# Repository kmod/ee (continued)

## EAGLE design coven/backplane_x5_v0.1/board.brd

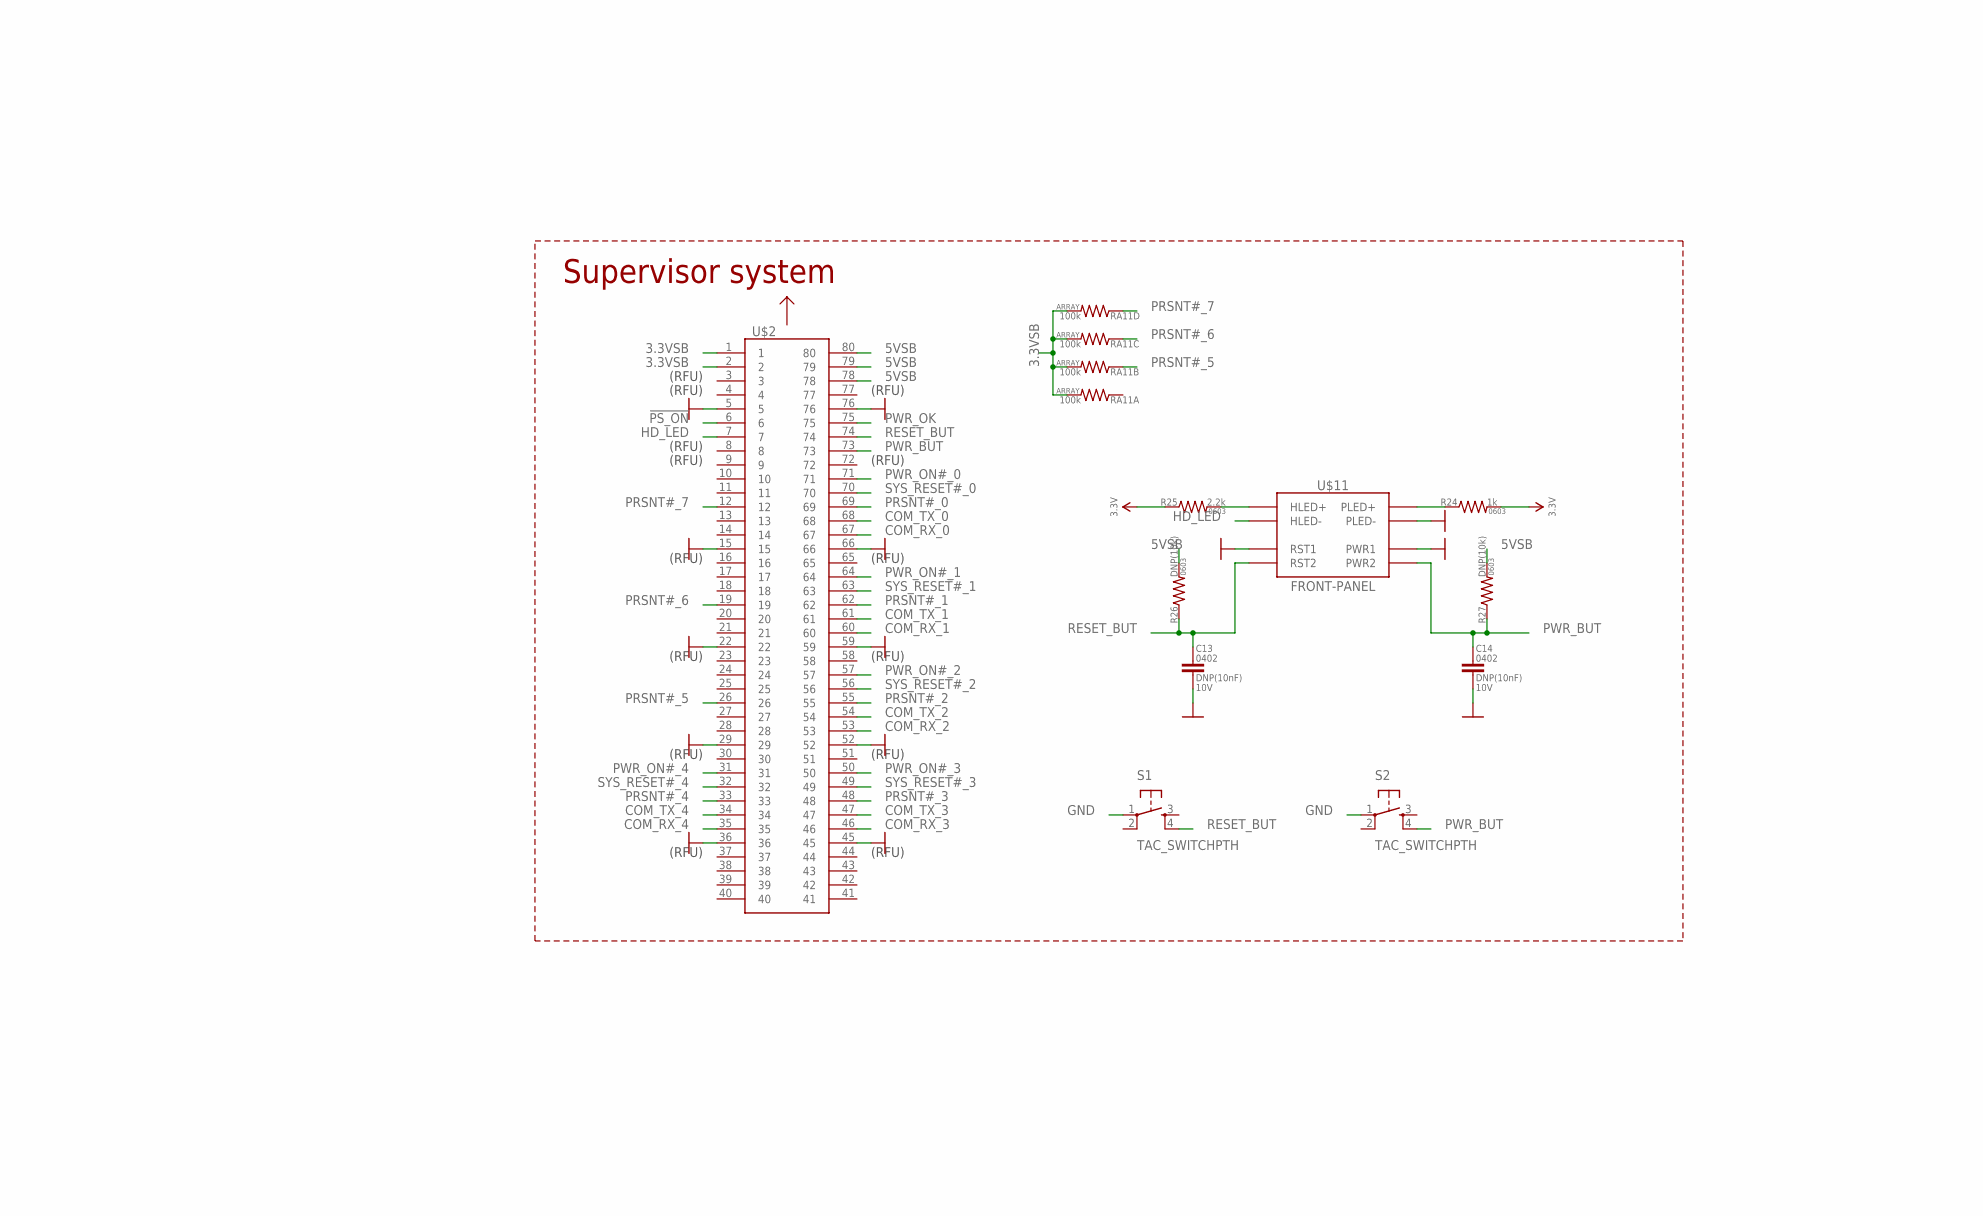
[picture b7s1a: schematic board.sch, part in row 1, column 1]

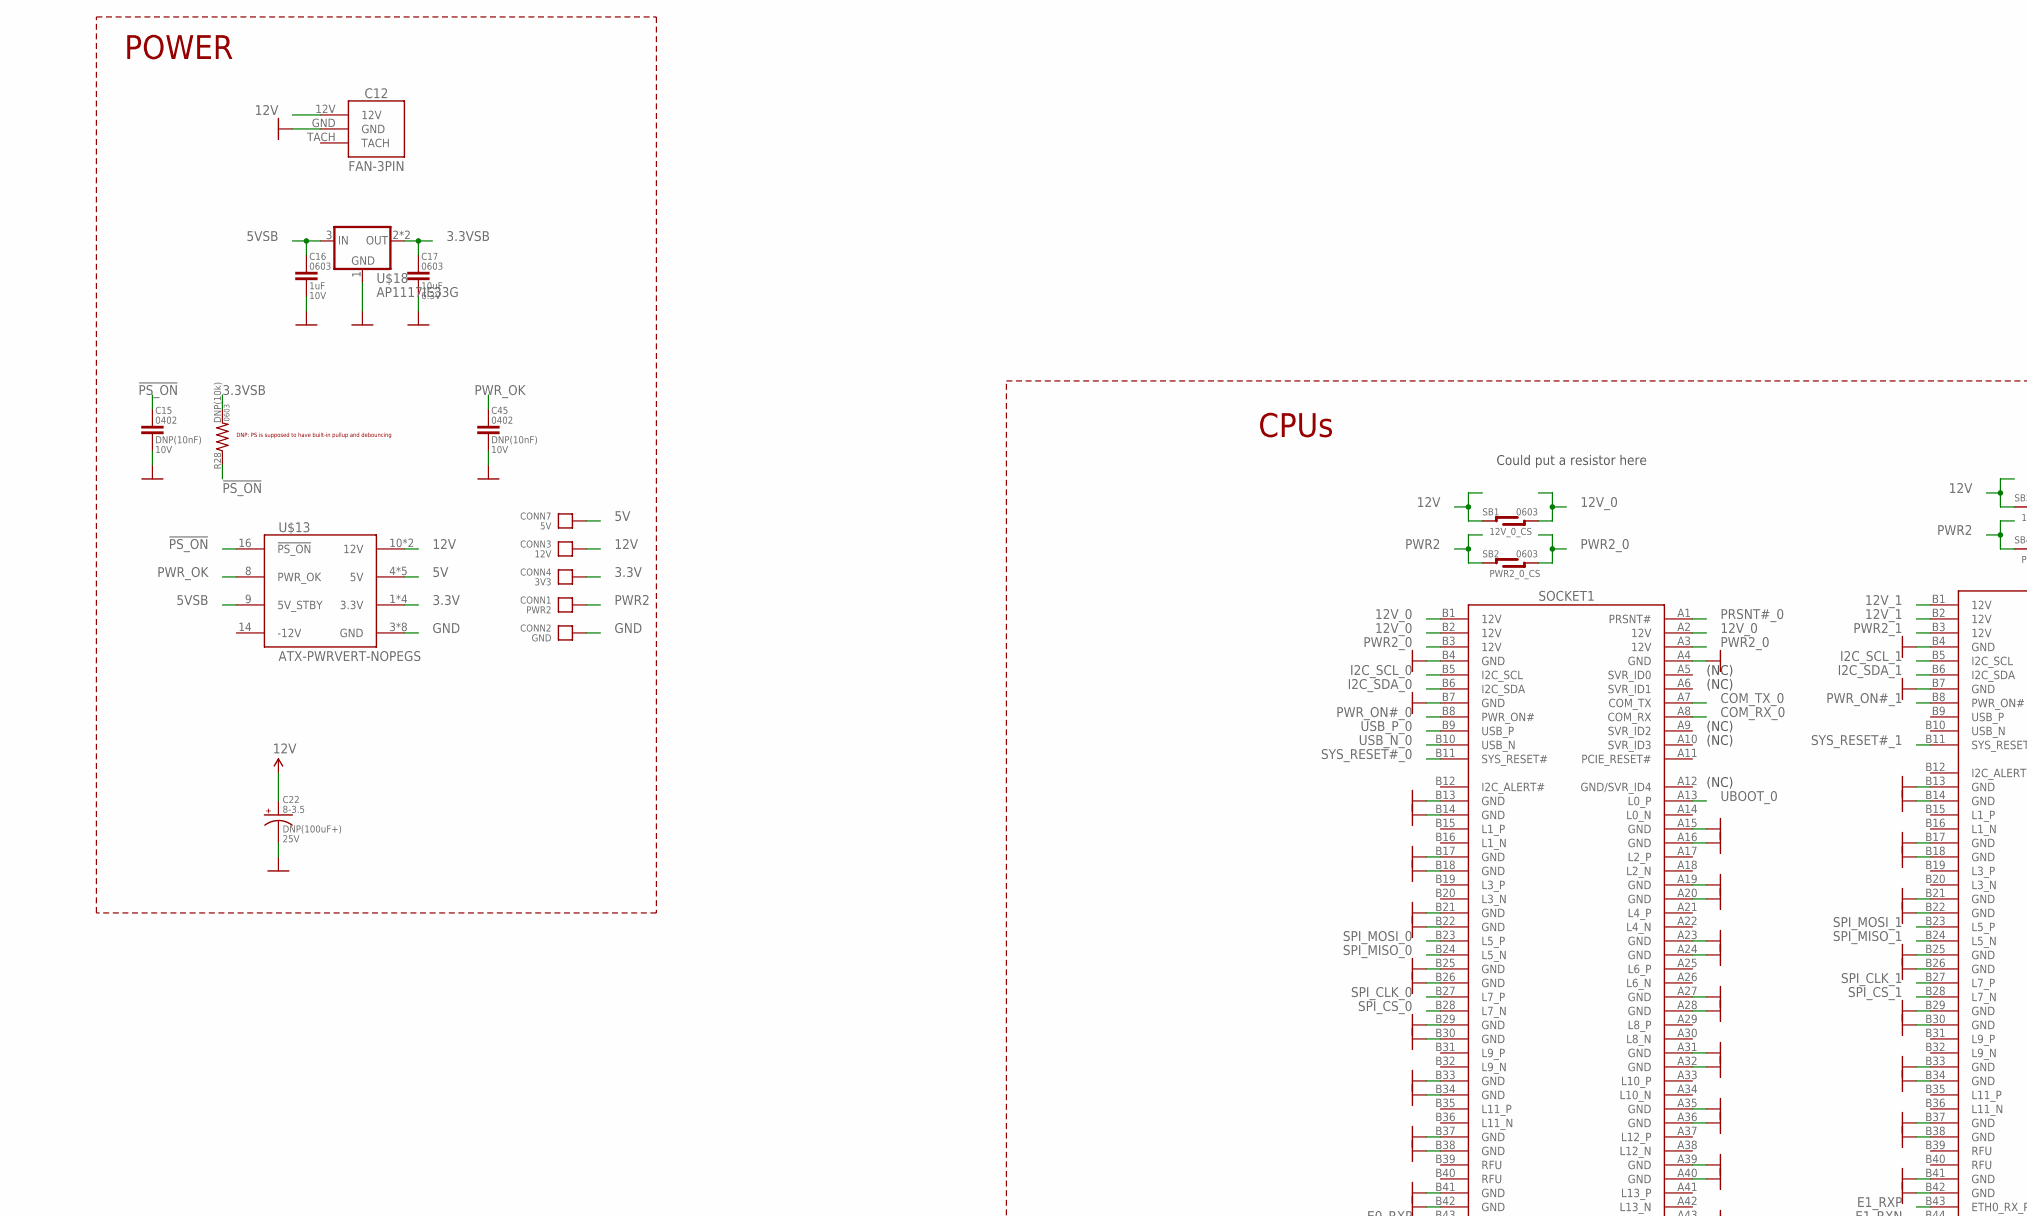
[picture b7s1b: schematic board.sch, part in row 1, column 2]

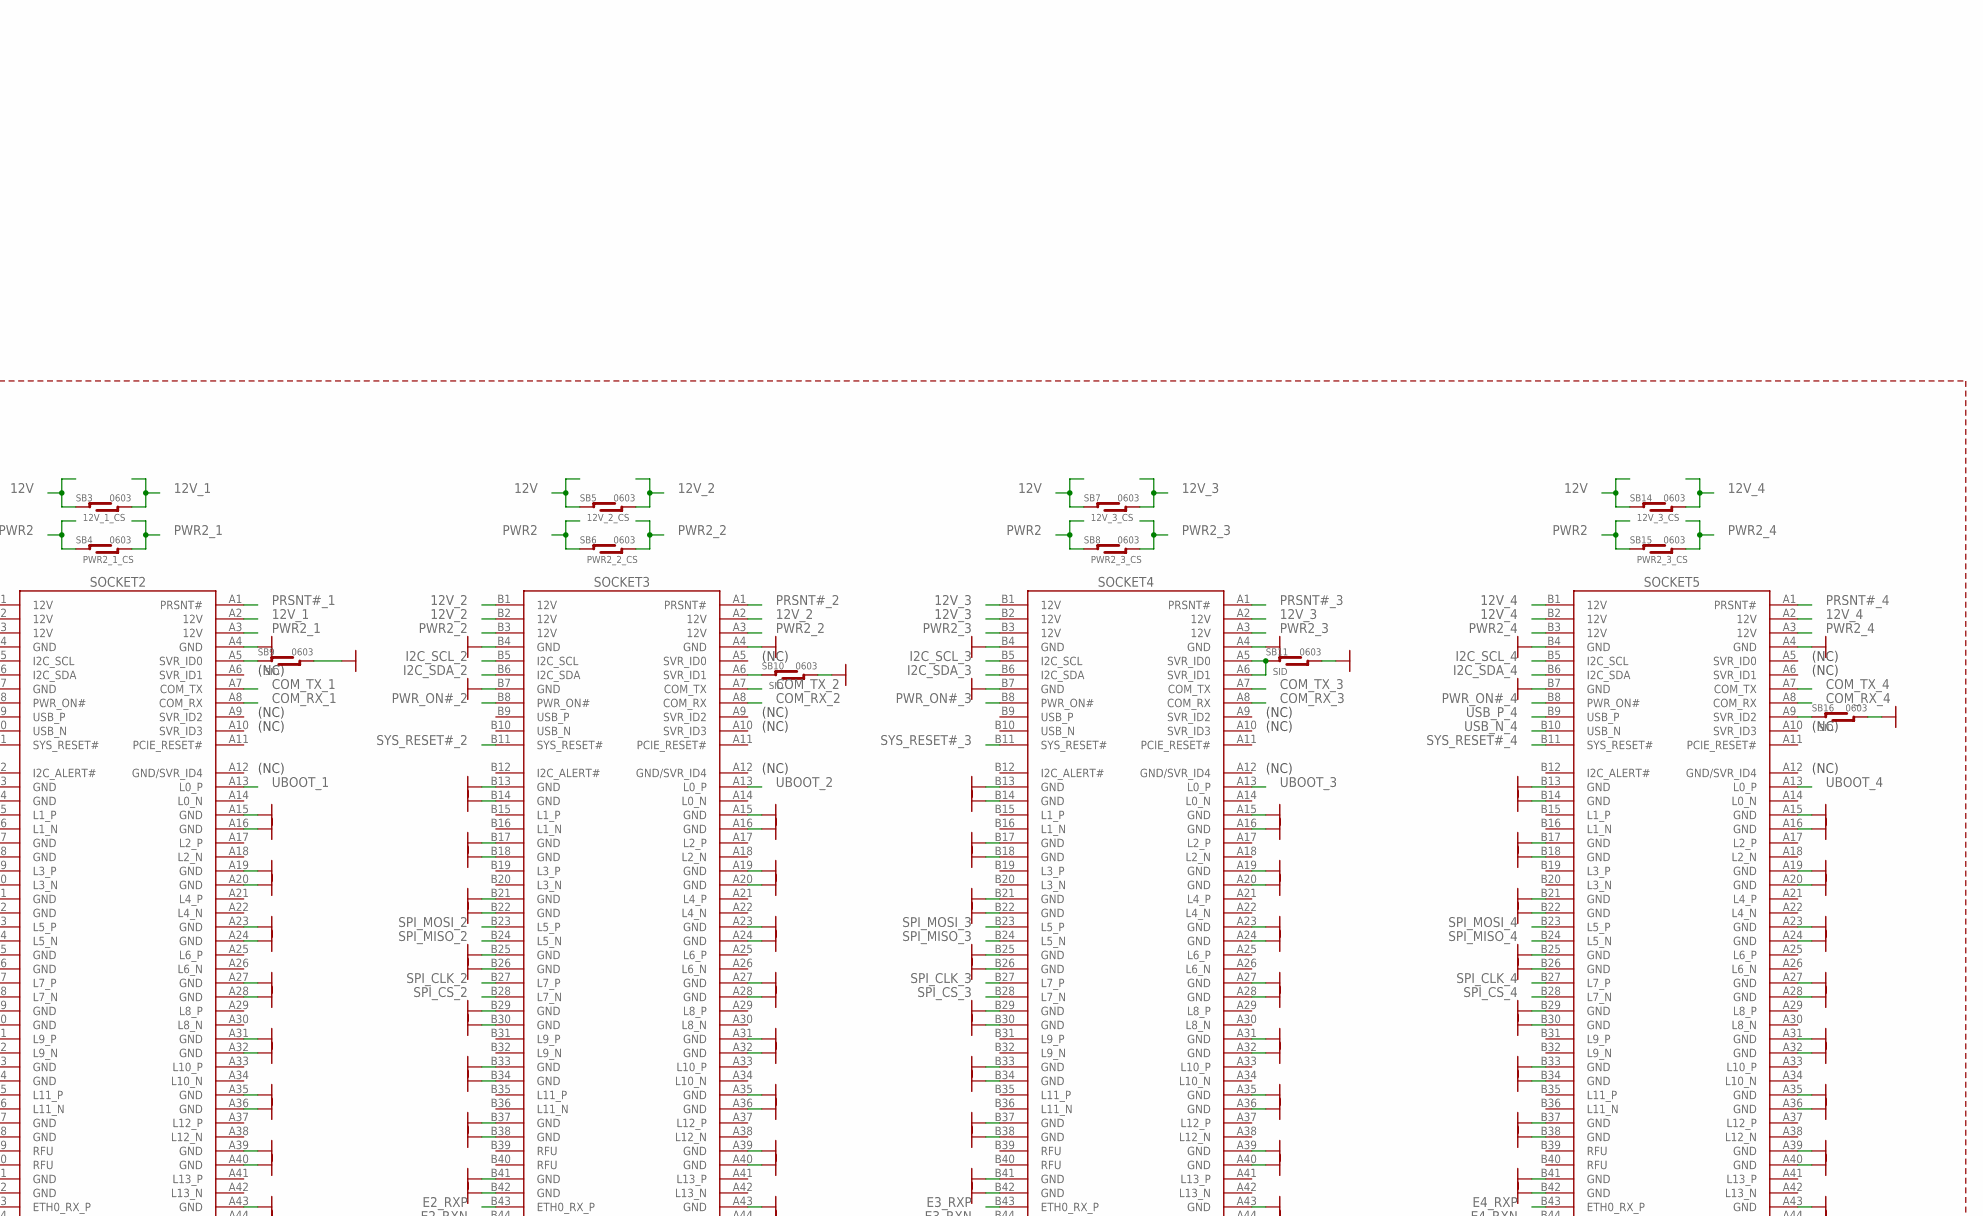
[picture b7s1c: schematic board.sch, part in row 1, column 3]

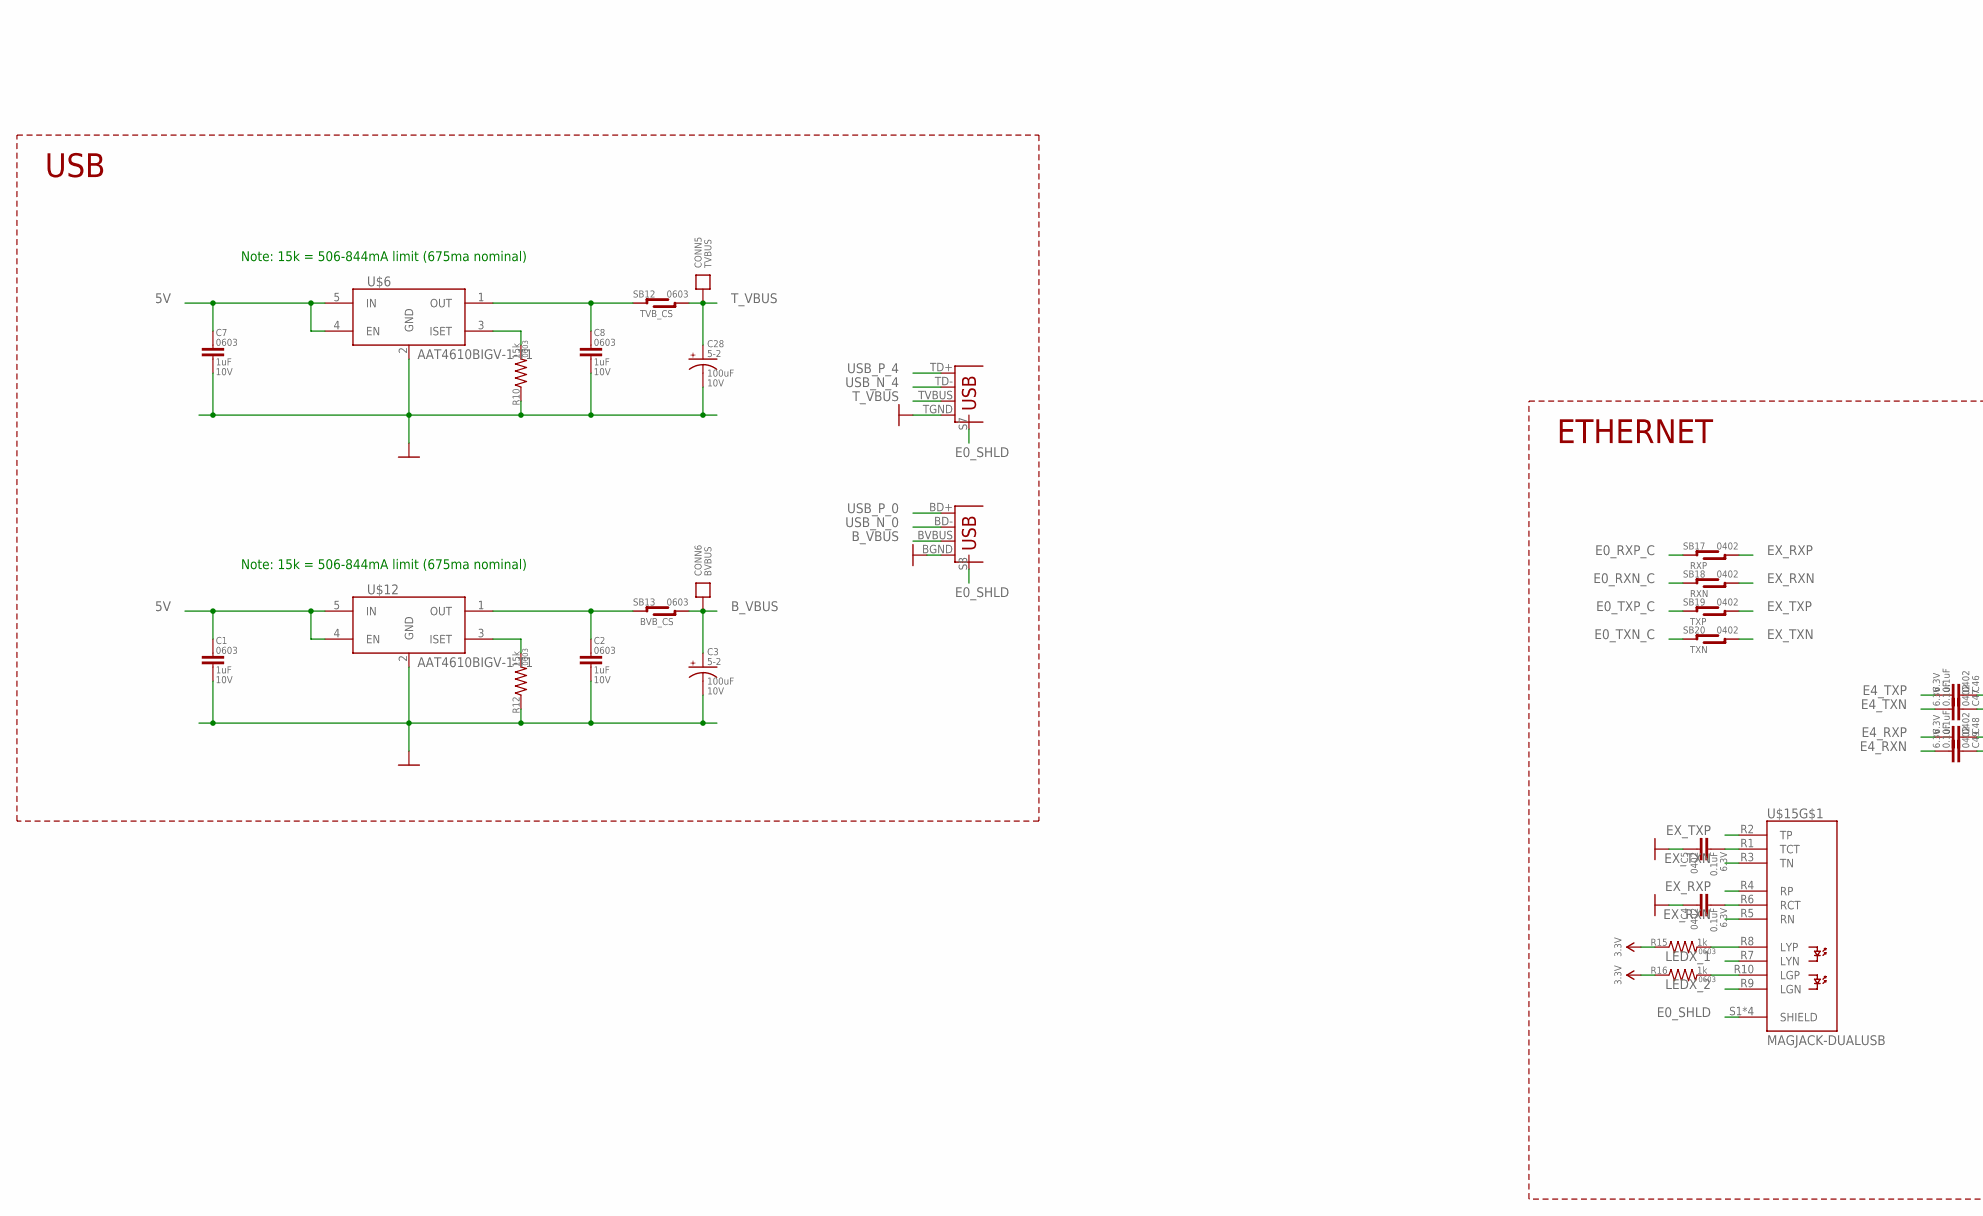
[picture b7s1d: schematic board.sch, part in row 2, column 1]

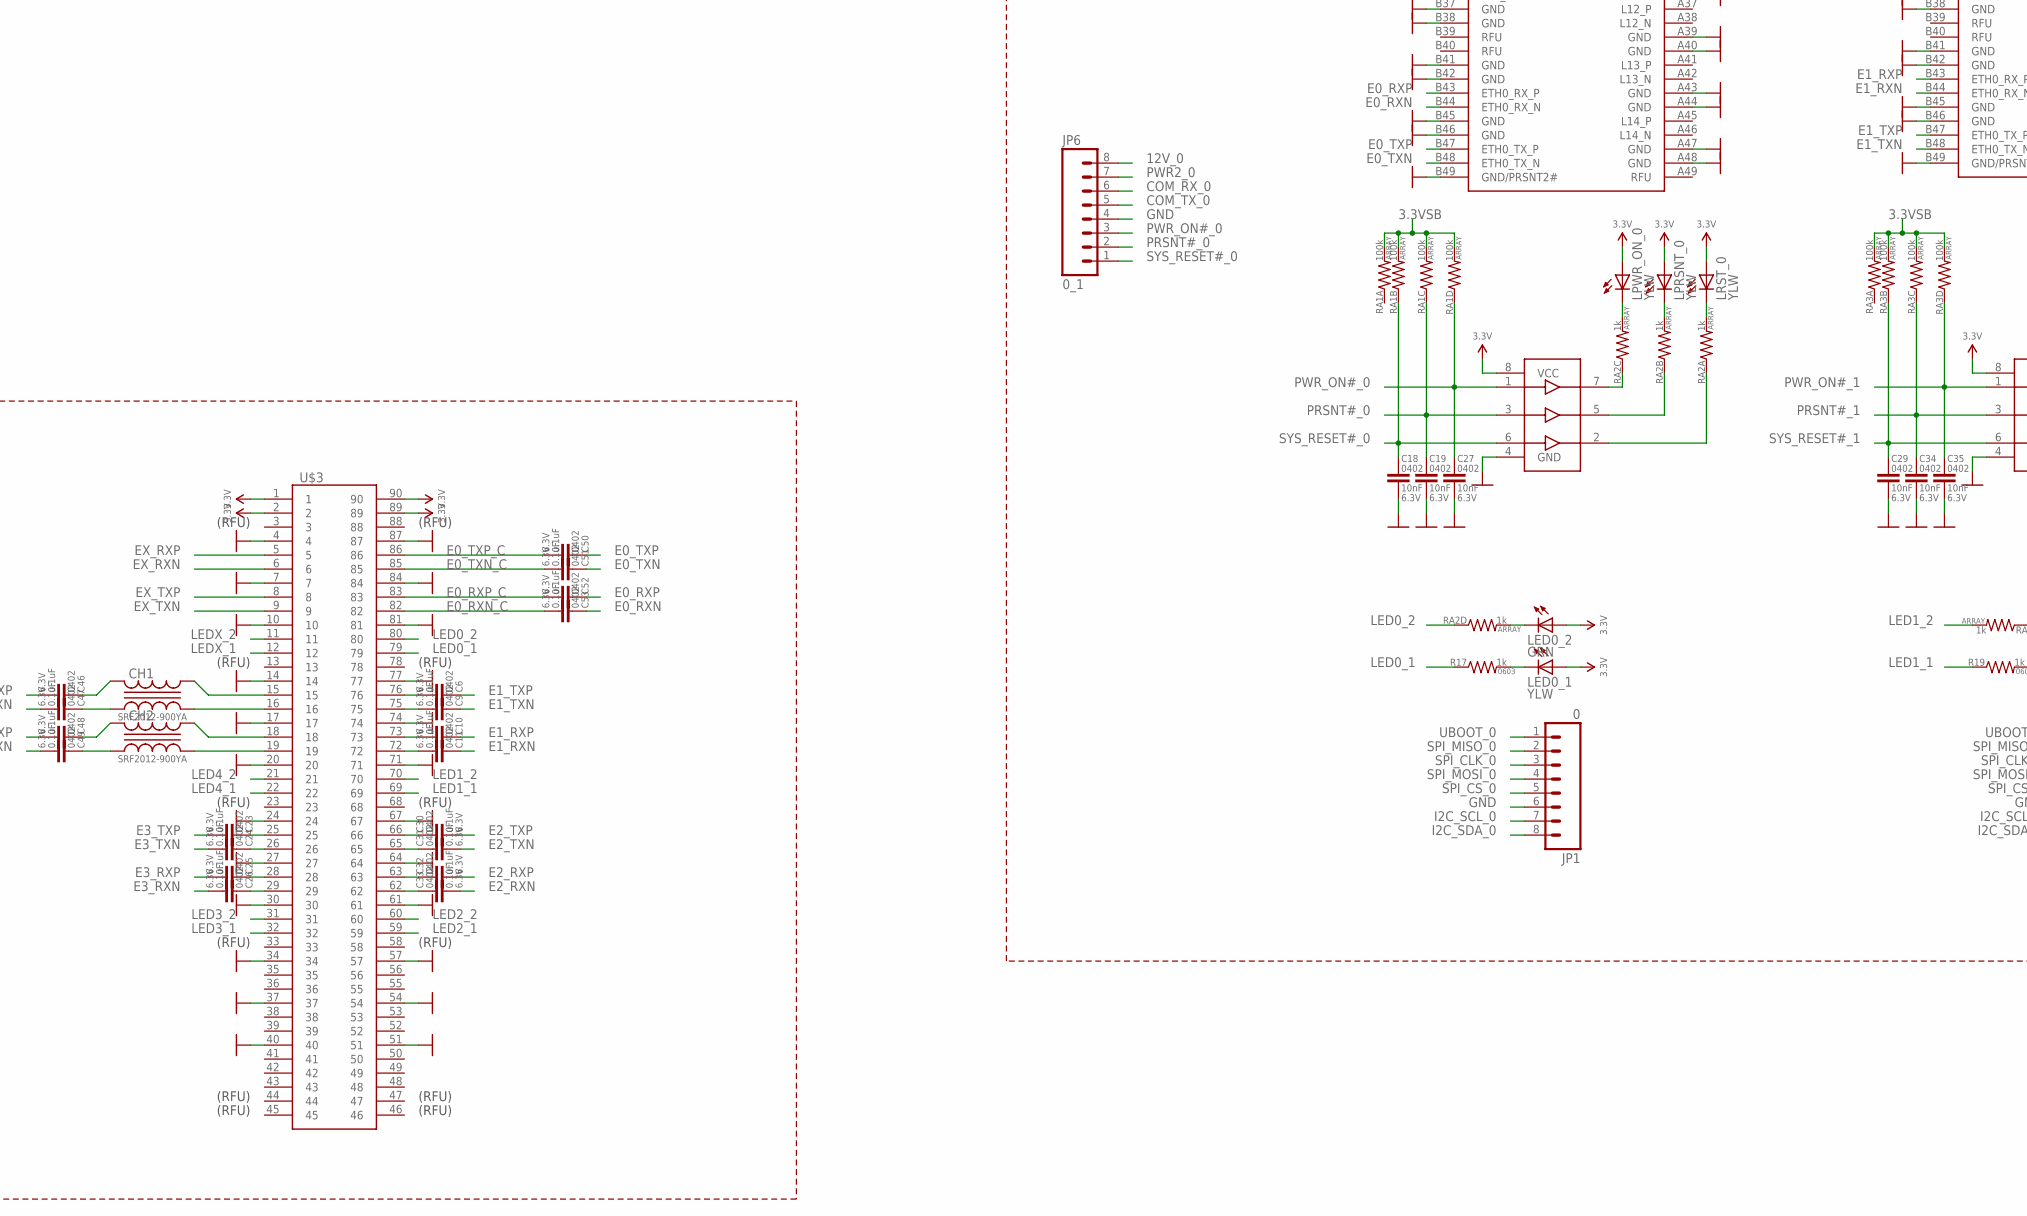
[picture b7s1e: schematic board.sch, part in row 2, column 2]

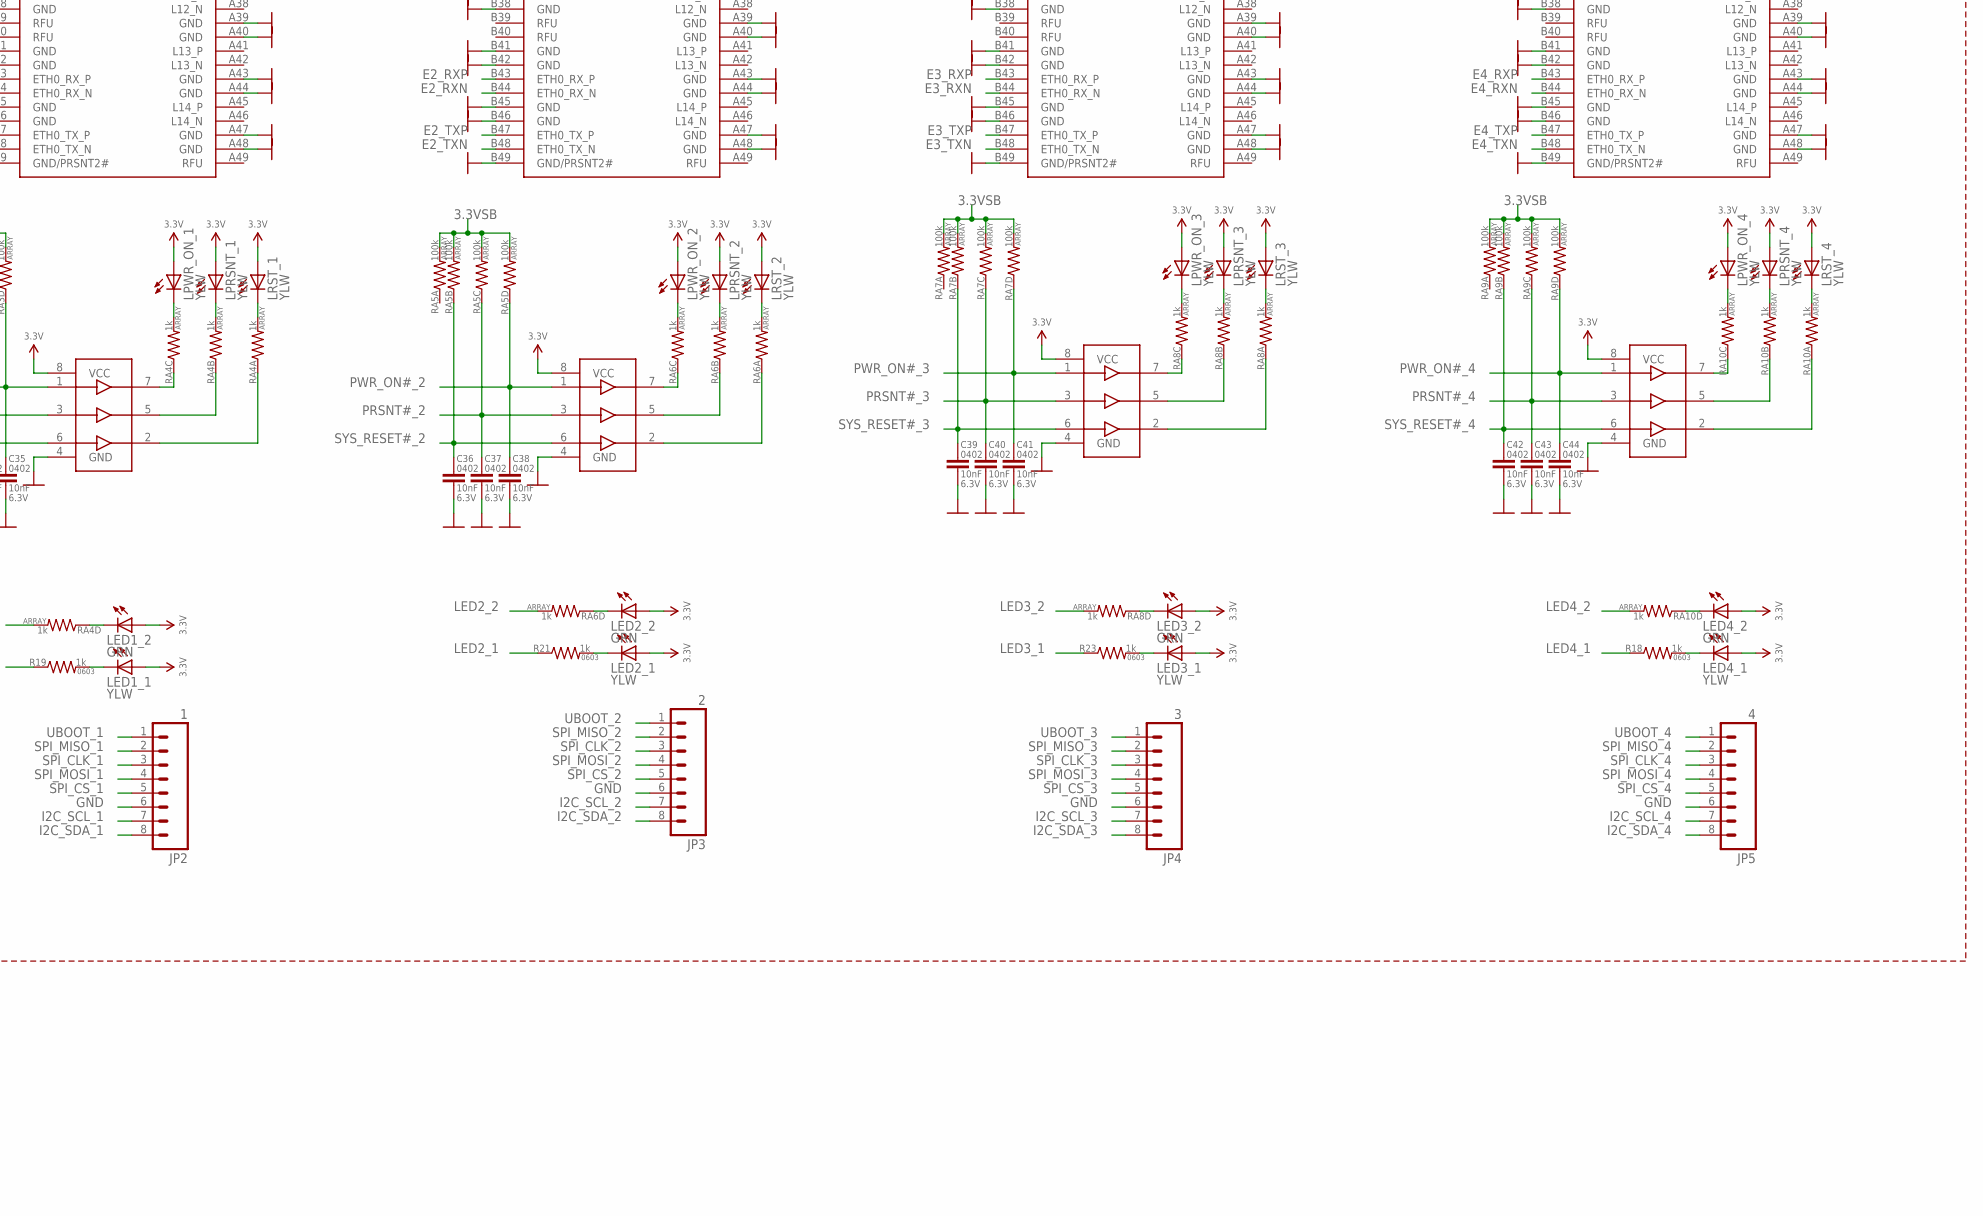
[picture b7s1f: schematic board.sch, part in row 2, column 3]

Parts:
C1, C2, C7, C8, C16: 1uF; 0603-CAP; VOLTAGE 10V
C3, C28: 100uF; CAP-5-2; VOLTAGE 10V
C4, C5, C6, C9, C10, C11, C23, C24, C25, C26, C30, C31, C32, C33, C46, C47, C48, C49, C50, C51, C52, C53: 0.1uF; 0402-CAP
C12: FAN-3PIN
C13, C14, C15, C45: DNP(10nF); 0402-CAP; VOLTAGE 10V
C17: 10uF; 0603-CAP
C18, C19, C27, C29, C34, C35, C36, C37, C38, C39, C40, C41, C42, C43, C44: 10nF; 0402-CAP
C22: DNP(100uF+); CAP-8-3.5; VOLTAGE 25V
CH1, CH2: SRF2012-900YA; SRF2012A
CONN1: PWR2; HOLE_18AWG
CONN2: GND; HOLE_18AWG
CONN3: 12V; HOLE_18AWG
CONN4: 3V3; HOLE_18AWG
CONN5: TVBUS; HOLE_22AWG
CONN6: BVBUS; HOLE_22AWG
CONN7: 5V; HOLE_18AWG
IC1, IC2, IC3, IC4, IC5: 74X3G34; TSSOP8
JP1: 0; 1X08
JP2: 1; 1X08
JP3: 2; 1X08
JP4: 3; 1X08
JP5: 4; 1X08
JP6: 0_1; 1X08
LED0_1, LED1_1, LED2_1, LED3_1, LED4_1: YLW; 0603_LED
LED0_2, LED1_2, LED2_2, LED3_2, LED4_2: GRN; 0603_LED
LPRSNT_0, LPRSNT_1, LPRSNT_2, LPRSNT_3, LPRSNT_4: YLW; 0603_LED
LPWR_ON_0, LPWR_ON_1, LPWR_ON_2, LPWR_ON_3, LPWR_ON_4: YLW; 0603_LED
LRST_0, LRST_1, LRST_2, LRST_3, LRST_4: YLW; 0603_LED
R10, R12: 15k; 0603-RES
R15, R16, R17, R18, R19, R21, R23, R24: 1k; 0603-RES
R25: 2.2k; 0603-RES
R26, R27, R28: DNP(10k); 0603-RES
RA1, RA3, RA5, RA7, RA9, RA11: 100k; 0603-ARV
RA2, RA4, RA6, RA8, RA10: 1k; 0603-ARV
S1, S2: TAC_SWITCHPTH; TACTILE-PTH
SB1: 12V_0_CS; SB-0603
SB2: PWR2_0_CS; SB-0603
SB3: 12V_1_CS; SB-0603
SB4: PWR2_1_CS; SB-0603
SB5: 12V_2_CS; SB-0603
SB6: PWR2_2_CS; SB-0603
SB7, SB14: 12V_3_CS; SB-0603
SB8, SB15: PWR2_3_CS; SB-0603
SB9, SB10, SB11, SB16: SID; SB-0603
SB12: TVB_CS; SB-0603
SB13: BVB_CS; SB-0603
SB17: RXP; SB-0402
SB18: RXN; SB-0402
SB19: TXP; SB-0402
SB20: TXN; SB-0402
SOCKET1, SOCKET2, SOCKET3, SOCKET4, SOCKET5: COVEN-V1CONN; CVN-V1-CONN
U$2: DF40-80RCP; DF40-RCP-80
U$3: DF40-90RCP; DF40-RCP-90
U$6, U$12: AAT4610BIGV-1-T1; SOT23-5
U$11: FRONT-PANEL
U$13: ATX-PWRVERT-NOPEGS; ATX-24-VERT-NOPEGS
U$15: MAGJACK-DUALUSB
U$18: AP1117IE33G; SOT223

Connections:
3.3V: CONN4.P$1, IC1.8 (VCC), IC2.8 (VCC), IC3.8 (VCC), IC4.8 (VCC), IC5.8 (VCC), LED0_1.A, LED0_2.A, LED1_1.A, LED1_2.A, LED2_1.A, LED2_2.A, LED3_1.A, LED3_2.A, LED4_1.A, LED4_2.A, LPRSNT_0.A, LPRSNT_1.A, LPRSNT_2.A, LPRSNT_3.A, LPRSNT_4.A, LPWR_ON_0.A, LPWR_ON_1.A, LPWR_ON_2.A, LPWR_ON_3.A, LPWR_ON_4.A, LRST_0.A, LRST_1.A, LRST_2.A, LRST_3.A, LRST_4.A, R15.1, R16.1, R24.2, R25.1, U$3.1, U$3.2, U$3.89, U$3.90, U$13.1 (3.3V), U$13.2 (3.3V), U$13.12 (3.3V), U$13.13 (3.3V)
3.3VSB: C17.1, R28.2, RA1.5 (2), RA1.6 (2), RA1.7 (2), RA1.8 (2), RA3.5 (2), RA3.6 (2), RA3.7 (2), RA3.8 (2), RA5.5 (2), RA5.6 (2), RA5.7 (2), RA5.8 (2), RA7.5 (2), RA7.6 (2), RA7.7 (2), RA7.8 (2), RA9.5 (2), RA9.6 (2), RA9.7 (2), RA9.8 (2), RA11.5 (2), RA11.6 (2), RA11.7 (2), RA11.8 (2), U$2.1, U$2.2, U$18.2 (OUT), U$18.4 (OUT)
5V: C1.1, C7.1, CONN7.P$1, U$6.4 (EN), U$6.5 (IN), U$12.4 (EN), U$12.5 (IN), U$13.4 (5V), U$13.6 (5V), U$13.21 (5V), U$13.22 (5V), U$13.23 (5V)
5VSB: C16.1, R26.2, R27.2, U$2.78, U$2.79, U$2.80, U$13.9 (5V_STBY), U$18.3 (IN)
12V: C12.12V, C22.1 (+), CONN3.P$1, SB1.L1, SB1.L2, SB3.L1, SB3.L2, SB5.L1, SB5.L2, SB7.L1, SB7.L2, SB14.L1, SB14.L2, U$13.10 (12V), U$13.11 (12V)
12V_0: JP6.8, SB1.R1, SB1.R2, SOCKET1.A2 (12V), SOCKET1.B1 (12V), SOCKET1.B2 (12V)
12V_1: SB3.R1, SB3.R2, SOCKET2.A2 (12V), SOCKET2.B1 (12V), SOCKET2.B2 (12V)
12V_2: SB5.R1, SB5.R2, SOCKET3.A2 (12V), SOCKET3.B1 (12V), SOCKET3.B2 (12V)
12V_3: SB7.R1, SB7.R2, SOCKET4.A2 (12V), SOCKET4.B1 (12V), SOCKET4.B2 (12V)
12V_4: SB14.R1, SB14.R2, SOCKET5.A2 (12V), SOCKET5.B1 (12V), SOCKET5.B2 (12V)
!PS_ON: C15.1, R28.1, U$2.6, U$13.16 (!PS_ON)
B_VBUS: C3.1 (+), CONN6.P, SB13.R1, SB13.R2, U$15.BVBUS (VBUS)
COM_RX_0: JP6.6, SOCKET1.A8 (COM_RX), U$2.67
COM_RX_1: SOCKET2.A8 (COM_RX), U$2.60
COM_RX_2: SOCKET3.A8 (COM_RX), U$2.53
COM_RX_3: SOCKET4.A8 (COM_RX), U$2.46
COM_RX_4: SOCKET5.A8 (COM_RX), U$2.35
COM_TX_0: JP6.5, SOCKET1.A7 (COM_TX), U$2.68
COM_TX_1: SOCKET2.A7 (COM_TX), U$2.61
COM_TX_2: SOCKET3.A7 (COM_TX), U$2.54
COM_TX_3: SOCKET4.A7 (COM_TX), U$2.47
COM_TX_4: SOCKET5.A7 (COM_TX), U$2.34
E0_RXN: C53.1, SOCKET1.B44 (ETH0_RX_N)
E0_RXN_C: C53.2, SB18.L1, SB18.L2, U$3.82
E0_RXP: C52.1, SOCKET1.B43 (ETH0_RX_P)
E0_RXP_C: C52.2, SB17.L1, SB17.L2, U$3.83
E0_SHLD: U$15.S1 (SHIELD), U$15.S2 (SHIELD), U$15.S3 (SHIELD), U$15.S4 (SHIELD), U$15.S7 (SHELL), U$15.S8 (SHELL)
E0_TXN: C51.1, SOCKET1.B48 (ETH0_TX_N)
E0_TXN_C: C51.2, SB20.L1, SB20.L2, U$3.85
E0_TXP: C50.1, SOCKET1.B47 (ETH0_TX_P)
E0_TXP_C: C50.2, SB19.L1, SB19.L2, U$3.86
E1_RXN: C11.1, SOCKET2.B44 (ETH0_RX_N)
E1_RXP: C10.1, SOCKET2.B43 (ETH0_RX_P)
E1_TXN: C9.1, SOCKET2.B48 (ETH0_TX_N)
E1_TXP: C6.1, SOCKET2.B47 (ETH0_TX_P)
E2_RXN: C33.2, SOCKET3.B44 (ETH0_RX_N)
E2_RXP: C32.2, SOCKET3.B43 (ETH0_RX_P)
E2_TXN: C31.2, SOCKET3.B48 (ETH0_TX_N)
E2_TXP: C30.2, SOCKET3.B47 (ETH0_TX_P)
E3_RXN: C26.2, SOCKET4.B44 (ETH0_RX_N)
E3_RXP: C25.2, SOCKET4.B43 (ETH0_RX_P)
E3_TXN: C24.2, SOCKET4.B48 (ETH0_TX_N)
E3_TXP: C23.2, SOCKET4.B47 (ETH0_TX_P)
E4_RXN: C49.2, SOCKET5.B44 (ETH0_RX_N)
E4_RXP: C48.2, SOCKET5.B43 (ETH0_RX_P)
E4_TXN: C47.2, SOCKET5.B48 (ETH0_TX_N)
E4_TXP: C46.2, SOCKET5.B47 (ETH0_TX_P)
EX_RXN: SB18.R1, SB18.R2, U$3.6, U$15.R5 (RN)
EX_RXP: SB17.R1, SB17.R2, U$3.5, U$15.R4 (RP)
EX_TXN: SB20.R1, SB20.R2, U$3.9, U$15.R3 (TN)
EX_TXP: SB19.R1, SB19.R2, U$3.8, U$15.R2 (TP)
GND: C1.2, C2.2, C3.2 (-), C4.1, C5.1, C7.2, C8.2, C12.GND, C13.2, C14.2, C15.2, C16.2, C17.2, C18.2, C19.2, C22.2 (-), C27.2, C28.2 (-), C29.2, C34.2, C35.2, C36.2, C37.2, C38.2, C39.2, C40.2, C41.2, C42.2, C43.2, C44.2, C45.2, CONN2.P$1, IC1.4 (GND), IC2.4 (GND), IC3.4 (GND), IC4.4 (GND), IC5.4 (GND), JP1.6, JP2.6, JP3.6, JP4.6, JP5.6, JP6.4, R10.1, R12.1, S1.1, S2.1, SB9.R1, SB9.R2, SB10.R1, SB10.R2, SB11.R1, SB11.R2, SB16.R1, SB16.R2, SOCKET1.A4 (GND), SOCKET1.A15 (GND), SOCKET1.A16 (GND), SOCKET1.A19 (GND), SOCKET1.A20 (GND), SOCKET1.A23 (GND), SOCKET1.A24 (GND), SOCKET1.A27 (GND), SOCKET1.A28 (GND), SOCKET1.A31 (GND), SOCKET1.A32 (GND), SOCKET1.A35 (GND), SOCKET1.A36 (GND), SOCKET1.A39 (GND), SOCKET1.A40 (GND), SOCKET1.A43 (GND), SOCKET1.A44 (GND), SOCKET1.A47 (GND), SOCKET1.A48 (GND), SOCKET1.B4 (GND), SOCKET1.B7 (GND), SOCKET1.B13 (GND), SOCKET1.B14 (GND), SOCKET1.B17 (GND), SOCKET1.B18 (GND), SOCKET1.B21 (GND), SOCKET1.B22 (GND), SOCKET1.B25 (GND), SOCKET1.B26 (GND), SOCKET1.B29 (GND), SOCKET1.B30 (GND), SOCKET1.B33 (GND), SOCKET1.B34 (GND), SOCKET1.B37 (GND), SOCKET1.B38 (GND), SOCKET1.B41 (GND), SOCKET1.B42 (GND), SOCKET1.B45 (GND), SOCKET1.B46 (GND), SOCKET1.B49 (GND/PRSNT2#), SOCKET2.A4 (GND), SOCKET2.A15 (GND), SOCKET2.A16 (GND), SOCKET2.A19 (GND), SOCKET2.A20 (GND), SOCKET2.A23 (GND), SOCKET2.A24 (GND), SOCKET2.A27 (GND), SOCKET2.A28 (GND), SOCKET2.A31 (GND), SOCKET2.A32 (GND), SOCKET2.A35 (GND), SOCKET2.A36 (GND), SOCKET2.A39 (GND), SOCKET2.A40 (GND), SOCKET2.A43 (GND), SOCKET2.A44 (GND), SOCKET2.A47 (GND), SOCKET2.A48 (GND), SOCKET2.B4 (GND), SOCKET2.B7 (GND), SOCKET2.B13 (GND), SOCKET2.B14 (GND), SOCKET2.B17 (GND), SOCKET2.B18 (GND), SOCKET2.B21 (GND), SOCKET2.B22 (GND), SOCKET2.B25 (GND), SOCKET2.B26 (GND), SOCKET2.B29 (GND), SOCKET2.B30 (GND), SOCKET2.B33 (GND), SOCKET2.B34 (GND), SOCKET2.B37 (GND), SOCKET2.B38 (GND), SOCKET2.B41 (GND), SOCKET2.B42 (GND), SOCKET2.B45 (GND), SOCKET2.B46 (GND), SOCKET2.B49 (GND/PRSNT2#), SOCKET3.A4 (GND), SOCKET3.A15 (GND), SOCKET3.A16 (GND), SOCKET3.A19 (GND), SOCKET3.A20 (GND), SOCKET3.A23 (GND), SOCKET3.A24 (GND), SOCKET3.A27 (GND), SOCKET3.A28 (GND), SOCKET3.A31 (GND), SOCKET3.A32 (GND), SOCKET3.A35 (GND), SOCKET3.A36 (GND), SOCKET3.A39 (GND), SOCKET3.A40 (GND), SOCKET3.A43 (GND), SOCKET3.A44 (GND), SOCKET3.A47 (GND), SOCKET3.A48 (GND), SOCKET3.B4 (GND), SOCKET3.B7 (GND), SOCKET3.B13 (GND), SOCKET3.B14 (GND), SOCKET3.B17 (GND), SOCKET3.B18 (GND), SOCKET3.B21 (GND), SOCKET3.B22 (GND), SOCKET3.B25 (GND), SOCKET3.B26 (GND), SOCKET3.B29 (GND), SOCKET3.B30 (GND), SOCKET3.B33 (GND), SOCKET3.B34 (GND), SOCKET3.B37 (GND), SOCKET3.B38 (GND), SOCKET3.B41 (GND), SOCKET3.B42 (GND), SOCKET3.B45 (GND), SOCKET3.B46 (GND), SOCKET3.B49 (GND/PRSNT2#), SOCKET4.A4 (GND), SOCKET4.A15 (GND), SOCKET4.A16 (GND), SOCKET4.A19 (GND), SOCKET4.A20 (GND)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
HD_LED: U$2.7, U$11.HDLED- (HLED-)
HOST_VBUS_U: C8.1, SB12.L1, SB12.L2, U$6.1 (OUT)
HOST_VBUS_U1: C2.1, SB13.L1, SB13.L2, U$12.1 (OUT)
I2C_SCL_0: JP1.7, SOCKET1.B5 (I2C_SCL)
I2C_SCL_1: JP2.7, SOCKET2.B5 (I2C_SCL)
I2C_SCL_2: JP3.7, SOCKET3.B5 (I2C_SCL)
I2C_SCL_3: JP4.7, SOCKET4.B5 (I2C_SCL)
I2C_SCL_4: JP5.7, SOCKET5.B5 (I2C_SCL)
I2C_SDA_0: JP1.8, SOCKET1.B6 (I2C_SDA)
I2C_SDA_1: JP2.8, SOCKET2.B6 (I2C_SDA)
I2C_SDA_2: JP3.8, SOCKET3.B6 (I2C_SDA)
I2C_SDA_3: JP4.8, SOCKET4.B6 (I2C_SDA)
I2C_SDA_4: JP5.8, SOCKET5.B6 (I2C_SDA)
LED0_1: R17.1, U$3.79
LED0_2: RA2.4 (1), U$3.80
LED1_1: R19.1, U$3.69
LED1_2: RA4.5 (2), U$3.70
LED2_1: R21.1, U$3.59
LED2_2: RA6.5 (2), U$3.60
LED3_1: R23.1, U$3.32
LED3_2: RA8.5 (2), U$3.31
LED4_1: R18.1, U$3.22
LED4_2: RA10.5 (2), U$3.21
LEDX_1: U$3.12, U$15.R7 (LYN)
LEDX_2: U$3.11, U$15.R9 (LGN)
unnamed: SB9.L1, SB9.L2, SOCKET2.A5 (SVR_ID0)
unnamed: SB11.L1, SB11.L2, SOCKET4.A5 (SVR_ID0), SOCKET4.A6 (SVR_ID1)
unnamed: SB10.L1, SB10.L2, SOCKET3.A6 (SVR_ID1)
unnamed: IC2.7 (1Y), RA4.3 (1)
unnamed: IC2.5 (2Y), RA4.2 (1)
unnamed: LPWR_ON_1.C, RA4.6 (2)
unnamed: LPWR_ON_0.C, RA2.6 (2)
unnamed: LPRSNT_0.C, RA2.7 (2)
unnamed: IC1.7 (1Y), RA2.3 (1)
unnamed: IC1.5 (2Y), RA2.2 (1)
unnamed: IC1.2 (3Y), RA2.1
unnamed: LRST_0.C, RA2.8 (2)
unnamed: LPRSNT_1.C, RA4.7 (2)
unnamed: IC2.2 (3Y), RA4.1
unnamed: LRST_1.C, RA4.8 (2)
unnamed: IC3.7 (1Y), RA6.3 (1)
unnamed: IC3.5 (2Y), RA6.2 (1)
unnamed: LPWR_ON_2.C, RA6.6 (2)
unnamed: LPRSNT_2.C, RA6.7 (2)
unnamed: IC3.2 (3Y), RA6.1
unnamed: LRST_2.C, RA6.8 (2)
unnamed: IC4.7 (1Y), RA8.3 (1)
unnamed: IC4.5 (2Y), RA8.2 (1)
unnamed: LPWR_ON_3.C, RA8.6 (2)
unnamed: LPRSNT_3.C, RA8.7 (2)
unnamed: IC4.2 (3Y), RA8.1
unnamed: LRST_3.C, RA8.8 (2)
unnamed: LED4_1.C, R18.2
unnamed: C11.2, U$3.72
unnamed: R10.2, U$6.3 (ISET)
unnamed: R12.2, U$12.3 (ISET)
unnamed: C5.2, U$15.R1 (TCT)
unnamed: C4.2, U$15.R6 (RCT)
unnamed: R25.2, U$11.HDLED+ (HLED+)
unnamed: R15.2, U$15.R8 (LYP)
unnamed: SB16.L1, SB16.L2, SOCKET5.A9 (SVR_ID2)
unnamed: IC5.7 (1Y), RA10.3 (1)
unnamed: IC5.5 (2Y), RA10.2 (1)
unnamed: R16.2, U$15.R10 (LGP)
unnamed: C6.2, U$3.76
unnamed: R24.1, U$11.PLED+
unnamed: CH2.3, U$3.19
unnamed: C9.2, U$3.75
unnamed: CH2.2, U$3.18
unnamed: CH1.3, U$3.16
unnamed: LPWR_ON_4.C, RA10.6 (2)
unnamed: LPRSNT_4.C, RA10.7 (2)
unnamed: C33.1, U$3.62
unnamed: C32.1, U$3.63
unnamed: C31.1, U$3.65
unnamed: C30.1, U$3.66
unnamed: C25.1, U$3.28
unnamed: C24.1, U$3.26
unnamed: C23.1, U$3.25
unnamed: LED0_1.C, R17.2
unnamed: LED0_2.C, RA2.5 (2)
unnamed: LED1_2.C, RA4.4 (1)
unnamed: LED1_1.C, R19.2
unnamed: LED2_2.C, RA6.4 (1)
unnamed: LED2_1.C, R21.2
unnamed: LED3_2.C, RA8.4 (1)
unnamed: LED3_1.C, R23.2
unnamed: IC5.2 (3Y), RA10.1
unnamed: LRST_4.C, RA10.8 (2)
unnamed: LED4_2.C, RA10.4 (1)
unnamed: CH1.2, U$3.15
unnamed: C46.1, CH1.1
unnamed: C47.1, CH1.4
unnamed: C48.1, CH2.1
unnamed: C49.1, CH2.4
unnamed: C10.2, U$3.73
unnamed: C26.1, U$3.29
PRSNT#_0: C19.1, IC1.3 (2A), JP6.2, RA1.3 (1), SOCKET1.A1 (PRSNT#), U$2.69
PRSNT#_1: C34.1, IC2.3 (2A), RA3.3 (1), SOCKET2.A1 (PRSNT#), U$2.62
PRSNT#_2: C37.1, IC3.3 (2A), RA5.3 (1), SOCKET3.A1 (PRSNT#), U$2.55
PRSNT#_3: C40.1, IC4.3 (2A), RA7.3 (1), SOCKET4.A1 (PRSNT#), U$2.48
PRSNT#_4: C43.1, IC5.3 (2A), RA9.3 (1), SOCKET5.A1 (PRSNT#), U$2.33
PRSNT#_5: RA11.2 (1), U$2.26
PRSNT#_6: RA11.3 (1), U$2.19
PRSNT#_7: RA11.4 (1), U$2.12
PWR2: CONN1.P$1, SB2.L1, SB2.L2, SB4.L1, SB4.L2, SB6.L1, SB6.L2, SB8.L1, SB8.L2, SB15.L1, SB15.L2
PWR2_0: JP6.7, SB2.R1, SB2.R2, SOCKET1.A3 (12V), SOCKET1.B3 (12V)
PWR2_1: SB4.R1, SB4.R2, SOCKET2.A3 (12V), SOCKET2.B3 (12V)
PWR2_2: SB6.R1, SB6.R2, SOCKET3.A3 (12V), SOCKET3.B3 (12V)
PWR2_3: SB8.R1, SB8.R2, SOCKET4.A3 (12V), SOCKET4.B3 (12V)
PWR2_4: SB15.R1, SB15.R2, SOCKET5.A3 (12V), SOCKET5.B3 (12V)
PWR_BUT: C14.1, R27.1, S2.4, U$2.73, U$11.PWR_2 (PWR2)
PWR_OK: C45.1, U$2.75, U$13.8 (PWR_OK)
PWR_ON#_0: C27.1, IC1.1 (1A), JP6.3, RA1.4 (1), SOCKET1.B8 (PWR_ON#), U$2.71
PWR_ON#_1: C35.1, IC2.1 (1A), RA3.4 (1), SOCKET2.B8 (PWR_ON#), U$2.64
PWR_ON#_2: C38.1, IC3.1 (1A), RA5.4 (1), SOCKET3.B8 (PWR_ON#), U$2.57
PWR_ON#_3: C41.1, IC4.1 (1A), RA7.4 (1), SOCKET4.B8 (PWR_ON#), U$2.50
PWR_ON#_4: C44.1, IC5.1 (1A), RA9.4 (1), SOCKET5.B8 (PWR_ON#), U$2.31
RESET_BUT: C13.1, R26.1, S1.4, U$2.74, U$11.RST_2 (RST2)
SPI_CLK_0: JP1.3, SOCKET1.B27 (L7_P)
SPI_CLK_1: JP2.3, SOCKET2.B27 (L7_P)
SPI_CLK_2: JP3.3, SOCKET3.B27 (L7_P)
SPI_CLK_3: JP4.3, SOCKET4.B27 (L7_P)
SPI_CLK_4: JP5.3, SOCKET5.B27 (L7_P)
SPI_CS_0: JP1.5, SOCKET1.B28 (L7_N)
SPI_CS_1: JP2.5, SOCKET2.B28 (L7_N)
SPI_CS_2: JP3.5, SOCKET3.B28 (L7_N)
SPI_CS_3: JP4.5, SOCKET4.B28 (L7_N)
SPI_CS_4: JP5.5, SOCKET5.B28 (L7_N)
SPI_MISO_0: JP1.2, SOCKET1.B24 (L5_N)
SPI_MISO_1: JP2.2, SOCKET2.B24 (L5_N)
SPI_MISO_2: JP3.2, SOCKET3.B24 (L5_N)
SPI_MISO_3: JP4.2, SOCKET4.B24 (L5_N)
SPI_MISO_4: JP5.2, SOCKET5.B24 (L5_N)
SPI_MOSI_0: JP1.4, SOCKET1.B23 (L5_P)
SPI_MOSI_1: JP2.4, SOCKET2.B23 (L5_P)
SPI_MOSI_2: JP3.4, SOCKET3.B23 (L5_P)
SPI_MOSI_3: JP4.4, SOCKET4.B23 (L5_P)
SPI_MOSI_4: JP5.4, SOCKET5.B23 (L5_P)
SYS_RESET#_0: C18.1, IC1.6 (3A), JP6.1, RA1.2 (1), SOCKET1.B11 (SYS_RESET#), U$2.70
SYS_RESET#_1: C29.1, IC2.6 (3A), RA3.2 (1), SOCKET2.B11 (SYS_RESET#), U$2.63
SYS_RESET#_2: C36.1, IC3.6 (3A), RA5.2 (1), SOCKET3.B11 (SYS_RESET#), U$2.56
SYS_RESET#_3: C39.1, IC4.6 (3A), RA7.2 (1), SOCKET4.B11 (SYS_RESET#), U$2.49
SYS_RESET#_4: C42.1, IC5.6 (3A), RA9.2 (1), SOCKET5.B11 (SYS_RESET#), U$2.32
T_VBUS: C28.1 (+), CONN5.P, SB12.R1, SB12.R2, U$15.TVBUS (VBUS)
UBOOT_0: JP1.1, SOCKET1.A13 (L0_P)
UBOOT_1: JP2.1, SOCKET2.A13 (L0_P)
UBOOT_2: JP3.1, SOCKET3.A13 (L0_P)
UBOOT_3: JP4.1, SOCKET4.A13 (L0_P)
UBOOT_4: JP5.1, SOCKET5.A13 (L0_P)
USB_N_0: SOCKET1.B10 (USB_N), U$15.BD- (D-)
USB_N_4: SOCKET5.B10 (USB_N), U$15.TD- (D-)
USB_P_0: SOCKET1.B9 (USB_P), U$15.BD+ (D+)
USB_P_4: SOCKET5.B9 (USB_P), U$15.TD+ (D+)

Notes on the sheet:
(NC)
Note: 15k = 506-844mA limit (675ma nominal)
(RFU)
DNP: PS is supposed to have built-in pullup and debouncing
Supervisor system
Could put a resistor here
USB
POWER
ETHERNET
CPUs
